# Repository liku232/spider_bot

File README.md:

# spider_bot
Let a servo based spider-bot walk, using a DE10lite and a raspberry pi

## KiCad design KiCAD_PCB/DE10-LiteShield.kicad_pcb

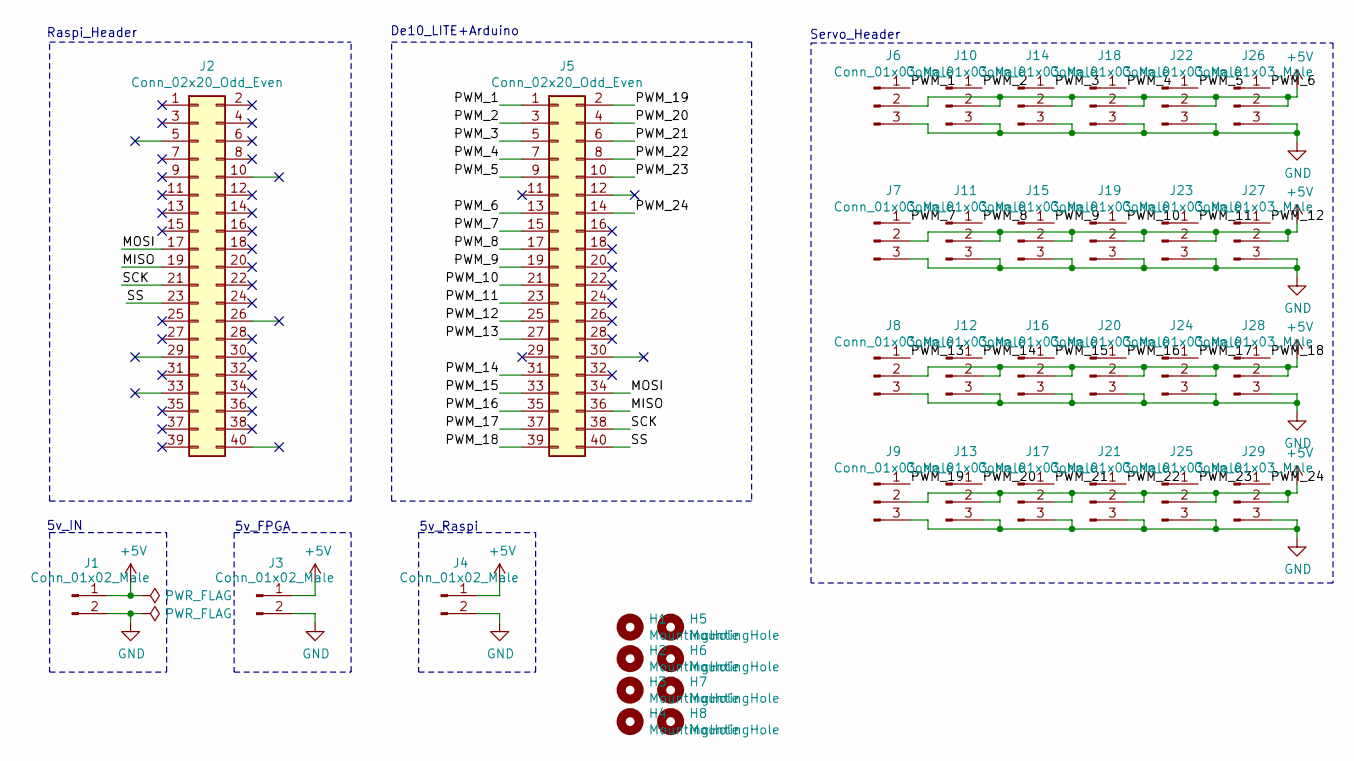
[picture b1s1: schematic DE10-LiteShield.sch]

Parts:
H1, H2, H3, H4, H5, H6, H7, H8: MountingHole; MountingHole_3.2mm_M3
J1, J3, J4: Conn_01x02_Male; PinHeader_1x02_P2.54mm_Vertical
J2, J5: Conn_02x20_Odd_Even; PinHeader_2x20_P2.54mm_Vertical
J6, J7, J8, J9, J10, J11, J12, J13, J14, J15, J16, J17, J18, J19, J20, J21, J22, J23, J24, J25, J26, J27, J28, J29: Conn_01x03_Male; PinHeader_1x03_P2.54mm_Vertical

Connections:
+5V: J1.1, J3.1, J4.1, J6.2, J7.2, J8.2, J9.2, J10.2, J11.2, J12.2, J13.2, J14.2, J15.2, J16.2, J17.2, J18.2, J19.2, J20.2, J21.2, J22.2, J23.2, J24.2, J25.2, J26.2, J27.2, J28.2, J29.2
/MISO: J2.19, J5.36
/MOSI: J2.17, J5.34
/PWM_1: J5.1, J6.1
/PWM_2: J5.3, J10.1
/PWM_3: J5.5, J14.1
/PWM_4: J5.7, J18.1
/PWM_5: J5.9, J22.1
/PWM_6: J5.13, J26.1
/PWM_7: J5.15, J7.1
/PWM_8: J5.17, J11.1
/PWM_9: J5.19, J15.1
/PWM_10: J5.21, J19.1
/PWM_11: J5.23, J23.1
/PWM_12: J5.25, J27.1
/PWM_13: J5.27, J8.1
/PWM_14: J5.31, J12.1
/PWM_15: J5.33, J16.1
/PWM_16: J5.35, J20.1
/PWM_17: J5.37, J24.1
/PWM_18: J5.39, J28.1
/PWM_19: J5.2, J9.1
/PWM_20: J5.4, J13.1
/PWM_21: J5.6, J17.1
/PWM_22: J5.8, J21.1
/PWM_23: J5.10, J25.1
/PWM_24: J5.14, J29.1
/SCK: J2.21, J5.38
/SS: J2.23, J5.40
GND: J1.2, J3.2, J4.2, J6.3, J7.3, J8.3, J9.3, J10.3, J11.3, J12.3, J13.3, J14.3, J15.3, J16.3, J17.3, J18.3, J19.3, J20.3, J21.3, J22.3, J23.3, J24.3, J25.3, J26.3, J27.3, J28.3, J29.3

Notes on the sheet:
Raspi_Header
De10_LITE+Arduino
5v_IN
Servo_Header
5v_FPGA
5v_Raspi

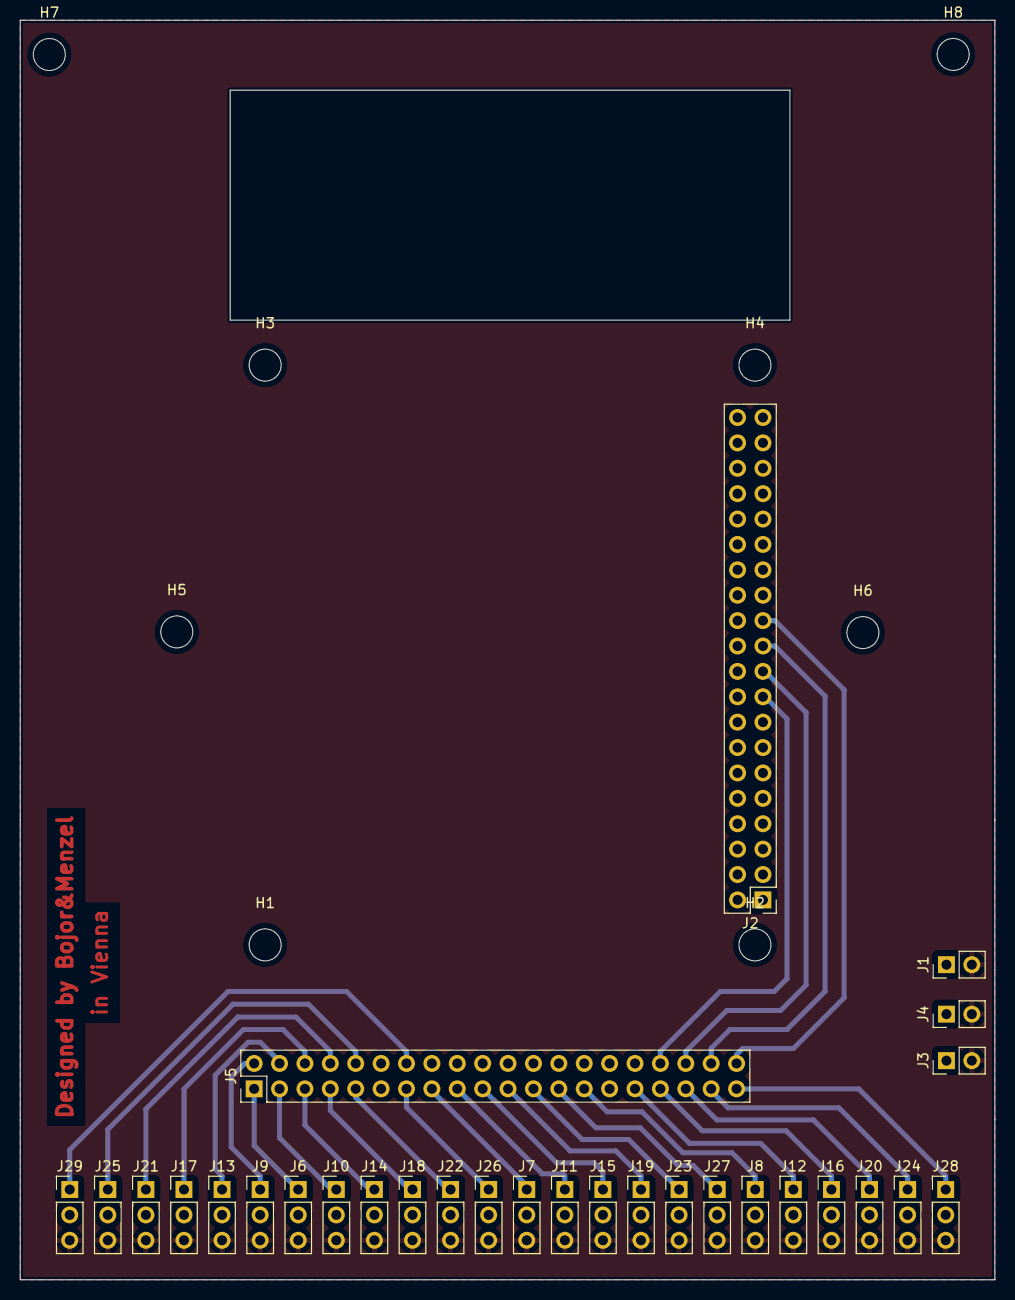
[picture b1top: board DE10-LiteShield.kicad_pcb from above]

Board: 2 copper layers, 97.5 x 126.0 mm, 37 parts (0 on the bottom side), 30 nets.

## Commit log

2021-11-15 Rename spi_slave.vhdl to spi_receiver/spi_slave.vhdl
2021-11-15 Rename ltb_spi_slave.vhdl to spi_receiver/ltb_spi_slave.vhdl
2021-11-15 Rename clock_divider.vhd to pwm_gen/clock_divider.vhd
2021-11-15 Create file
2021-11-15 Rename topleveldesign/incremental_deb/file to topleveldesign/incremental_db/file
2022-06-23 Create test
